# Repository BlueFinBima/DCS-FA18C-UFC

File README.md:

# DCS-FA18C-UFC
### This is a hardware and software project to build an Up Front Controller for the DCS F/A-18C Hornet

### Notes

The HT16K33 isn't too difficult to find, and can be picked up quite cheaply on AliExpress if you are prepared to wait.  The DLG2416 displays are quite expensive from 
typical vendors, however hunting around on ebay etc might result in more affordable sources.  They have a fixed character set which is unfortunate, however they remain useable and pleasing alternative to the 16 segment displays which the actual UFC requires.  If didn't manage to find suitable 16 segment displays of a physical size to work with this 
project.  The comms channel indicators are 16 segment displays (be careful not to buy 14 segment) but unfortunately I was unable to find displays which were not slanted - for me a minor issue.
* The ESP32 boards come in all sorts of shapes and sizes, and my controller board needs
a particular type of 38-pin board and I found to my cost that there were several boards with different widths.  I would expect [these boards](https://www.amazon.co.uk/AZDelivery-NodeMcu-CP2102-Development-including/dp/B074RGW2VQ/) to be the correct size.
* The green 16 segment LED displays now (2020) seem to be very hard to acquire.
* R2 and R5 on the controller board should only be installed as a last resort of the I2C is not stable without them
* The PCF8575 is a PCF8575PWR (TSSOP)
* D1 and D2 are BAT54CDW and not BAT54TW

### The Story
I would love to have a full Simpit for every aircraft – who
wouldn’t – but space / time / money all conspire against this.  I personally
feel that there is more immersion from the sensation of real switches, knobs
etc, but compromises are part of life.

I wanted a mix of virtual cockpit and some real devices so I
wrote a native F/A-18C interface for Helios, and I started a project to create
a hardware Up Front Controller.  This is what I am presenting here.   While the
3D printed UFC enclosure is very rough, hopefully you’ll get the idea of what I
am doing.  The UFC just has power going to it, and it has the potential to
drive future parts of the cockpit via i2c (I am aware of the limitations and
potential problems with the approach of using i2c, but it seems reliable in my
set up).   The UFC is controlled by an ESP32 board to get me the direct pins
and interrupts that I needed for the encoders.  Because there is only a single
power connecter to the UFC, it means that it can be removed from the set up
extremely quickly.  Likewise, the Thrustmaster Cougar MFDs are also very easy
to remove as they simply hang from the top of the screen, primarily to allow
hiding of the USB cables.  I rotated the rocker switches and 3D printed the
hangers so the MFDs sit over the top corners of the 23 inch Dell touch screen.

The UFC itself is pretty simple using DLG2416 displays (I
like the dots).  Unfortunately these do not have any programmable characters,
but the result is OK IMHO.  I would have preferred  16 and 7 segment displays,
but I could not find suitable devices.  The Comm Channel displays are 16
segment LED displays driven by the same HT16K33 that reads the keys and
switches.  Other things I would change if I ever revised the UFC design would
be to replace the 2 x volumes and the brightness knob with potentiometers and
put an i2c ADC onto the board – but I am happy enough with the encoders in the
current design that I’m not planning to do this.

I’m going to put a third Cougar MFD in for the AMPCD, but
I’m still considering how I can do this while keeping the mounting discrete.

#### 2020 Project Update
With two inidividuals (that I know of) successfully recreating this project, I chose to revisit
the facial.  I purchased a small SLA 3D printer which allowed me to print smaller key caps, and 
I was able to paint and use my 2.5W LED Laser to label these.  I also created new comm channel
selectors, as well as more harmonious knobs (ie not Mil Spec accurate) for the UFC.
My LED laser will not touch acrylic other than black, so the facia was cut from that material and 
white polystyrene sheet was then glued to the surface, and painted black.  The LED laser was then 
used to create the lettering.  While all of this is an improvement, I have to confess to not being 
very happy with this.   This is in part why the GitHub project has not been updated with these changes.

#### Thoughts about the future (July 2021)
Are there going to be further revisions to this project?  Well maybe.  I am considering a V3, primarily 
to see if I can improve the visuals of the displays, and to see if I can gain some level of crossover with
the AV-8B which has a similar UFC.  DLG2416's are expensive and difficult to get hold of.  16 segment LED displays
are also out of fashion, and green ones seem extremely rare.  I have created Eagle drawings for discrete 0603 / 0402
LED displays which can be charlieplexed and might be coaxed into looking like the 16-segment displays used in the 
real UFC.  I just need to finalise these plans, and pluck up the courage to use a PCBA service to build a prototype 
(I have neither the patience nor the skill to solder the volume to LEDs needed).  If I get around to getting a 
display prototyped *AND* I can work out how to make it look fit for purpose, then I will almost certainly begin
some work on a V3 of this UFC.

Controlling the very large number of LEDs will also be interesting, but I have been doing some prototyping and it does look possible.

### The History of this Project

I started out many years ago with the A-10C and Loz’s
profile for Helios which was a a great place to start.  After a while, I built
a real caution panel based on the Holtek HT16K33 which was driven by an Arduino
Pro Micro which communicated via a serial connection to a c# program which
talked to DCS.  Over time, the A-10C parts grew a bit and I had CMSC, CMSP,
UFC, NMSP and a few other panels.

The EOS project was a little too complex for my needs, and
while DCS-BIOS is a fantastic option, for a number of reasons, I have chosen to
stick with my own technology.

Fast forward a few years, and the Pro Micro and c# program
were replaced by an ESP8266 with more memory so that it had the capacity to do
all of the parsing needed and the wifi communication allowed direct connection
to the DCS exports.lua.  This was later replaced by an ESP32 board.

When the Hornet came out, I decided that I again wanted to
have a hybrid Helios cockpit, but I have always taken the view that offloading
as much work from my DCS PC so that it can concentrate  resources on DCS, was a
good thing.  Since I always have access to under-utilised PCs, I wanted the
virtual cockpit to be on a remote machine like I had with the A-10C. 
Unfortunately this ruled out Capt Zeen’s Hornet profile because it uses
keyboard commands which appear on the wrong PC, and the use of the A-10C Helios
interface requires a lot of processing in the exports.lua on the DCS machine.

I’m happy to make 3D parts visible on Fusion 360 on request.  Schematics etc are
Eagle format.

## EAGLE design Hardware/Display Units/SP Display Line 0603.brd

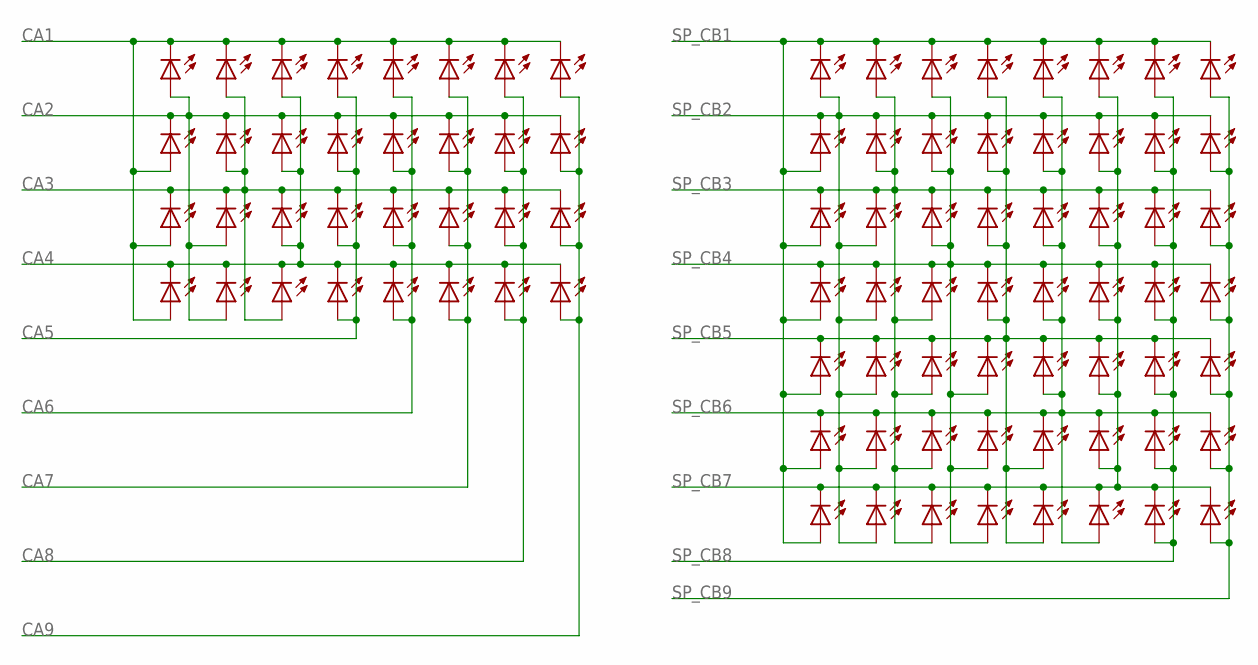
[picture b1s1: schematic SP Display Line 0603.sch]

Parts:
LED_A1, LED_A2: LEDSMT0603_1; CHIPLED_0603
LED_B1, LED_B2: LEDSMT0603_1; CHIPLED_0603
LED_C1, LED_C2: LEDSMT0603_1; CHIPLED_0603
LED_D1, LED_D2: LEDSMT0603_1; CHIPLED_0603
LED_DA1, LED_DA2, LED_DA3, LED_DA4, LED_DA5, LED_DA6, LED_DA7: LEDSMT0603_1; CHIPLED_0603
LED_DB1, LED_DB2, LED_DB3, LED_DB4, LED_DB5, LED_DB6, LED_DB7: LEDSMT0603_1; CHIPLED_0603
LED_DC1, LED_DC2, LED_DC3, LED_DC4, LED_DC5, LED_DC6, LED_DC7: LEDSMT0603_1; CHIPLED_0603
LED_DD1, LED_DD2, LED_DD3, LED_DD4, LED_DD5, LED_DD6, LED_DD7: LEDSMT0603_1; CHIPLED_0603
LED_DE1, LED_DE2, LED_DE3, LED_DE4, LED_DE5, LED_DE6, LED_DE7: LEDSMT0603_1; CHIPLED_0603
LED_DF1, LED_DF2, LED_DF3, LED_DF4, LED_DF5, LED_DF6, LED_DF7: LEDSMT0603_1; CHIPLED_0603
LED_DG1, LED_DG2, LED_DG3, LED_DG4, LED_DG5, LED_DG6, LED_DG7: LEDSMT0603_1; CHIPLED_0603
LED_DP1, LED_DP2, LED_DP3, LED_DP4, LED_DP5, LED_DP6, LED_DP7: LEDSMT0603_1; CHIPLED_0603
LED_E1, LED_E2: LEDSMT0603_1; CHIPLED_0603
LED_F1, LED_F2: LEDSMT0603_1; CHIPLED_0603
LED_G1, LED_G2: LEDSMT0603_1; CHIPLED_0603
LED_H1, LED_H2: LEDSMT0603_1; CHIPLED_0603
LED_K1, LED_K2: LEDSMT0603_1; CHIPLED_0603
LED_M1, LED_M2: LEDSMT0603_1; CHIPLED_0603
LED_N1, LED_N2: LEDSMT0603_1; CHIPLED_0603
LED_P1, LED_P2: LEDSMT0603_1; CHIPLED_0603
LED_R1, LED_R2: LEDSMT0603_1; CHIPLED_0603
LED_S1, LED_S2: LEDSMT0603_1; CHIPLED_0603
LED_T1, LED_T2: LEDSMT0603_1; CHIPLED_0603
LED_U1, LED_U2: LEDSMT0603_1; CHIPLED_0603

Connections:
CA1: LED_A1.C, LED_A2.A, LED_B1.C, LED_C1.C, LED_D1.C, LED_E1.C, LED_F1.C, LED_G1.C, LED_H1.C, LED_K1.A, LED_K2.A
CA2: LED_A1.A, LED_B2.A, LED_K1.C, LED_M1.C, LED_M2.A, LED_N1.C, LED_P1.C, LED_R1.C, LED_S1.C, LED_T1.C, LED_U1.C
CA3: LED_A2.C, LED_B1.A, LED_B2.C, LED_C2.C, LED_D2.C, LED_E2.C, LED_F2.C, LED_G2.C, LED_H2.C, LED_M1.A, LED_N2.A
CA4: LED_C1.A, LED_C2.A, LED_K2.C, LED_M2.C, LED_N1.A, LED_N2.C, LED_P2.C, LED_R2.C, LED_S2.C, LED_T2.C, LED_U2.C
CA5: LED_D1.A, LED_D2.A, LED_P1.A, LED_P2.A
CA6: LED_E1.A, LED_E2.A, LED_R1.A, LED_R2.A
CA7: LED_F1.A, LED_F2.A, LED_S1.A, LED_S2.A
CA8: LED_G1.A, LED_G2.A, LED_T1.A, LED_T2.A
CA9: LED_H1.A, LED_H2.A, LED_U1.A, LED_U2.A
SP_CB1: LED_DA1.C, LED_DA2.A, LED_DA3.A, LED_DA4.A, LED_DA5.A, LED_DA6.A, LED_DA7.A, LED_DB1.C, LED_DC1.C, LED_DD1.C, LED_DE1.C, LED_DF1.C, LED_DG1.C, LED_DP1.C
SP_CB2: LED_DA1.A, LED_DA2.C, LED_DB2.C, LED_DB3.A, LED_DB4.A, LED_DB5.A, LED_DB6.A, LED_DB7.A, LED_DC2.C, LED_DD2.C, LED_DE2.C, LED_DF2.C, LED_DG2.C, LED_DP2.C
SP_CB3: LED_DA3.C, LED_DB1.A, LED_DB2.A, LED_DB3.C, LED_DC3.C, LED_DC4.A, LED_DC5.A, LED_DC6.A, LED_DC7.A, LED_DD3.C, LED_DE3.C, LED_DF3.C, LED_DG3.C, LED_DP3.C
SP_CB4: LED_DA4.C, LED_DB4.C, LED_DC1.A, LED_DC2.A, LED_DC3.A, LED_DC4.C, LED_DD4.C, LED_DD5.A, LED_DD6.A, LED_DD7.A, LED_DE4.C, LED_DF4.C, LED_DG4.C, LED_DP4.C
SP_CB5: LED_DA5.C, LED_DB5.C, LED_DC5.C, LED_DD1.A, LED_DD2.A, LED_DD3.A, LED_DD4.A, LED_DD5.C, LED_DE5.C, LED_DE6.A, LED_DE7.A, LED_DF5.C, LED_DG5.C, LED_DP5.C
SP_CB6: LED_DA6.C, LED_DB6.C, LED_DC6.C, LED_DD6.C, LED_DE1.A, LED_DE2.A, LED_DE3.A, LED_DE4.A, LED_DE5.A, LED_DE6.C, LED_DF6.C, LED_DF7.A, LED_DG6.C, LED_DP6.C
SP_CB7: LED_DA7.C, LED_DB7.C, LED_DC7.C, LED_DD7.C, LED_DE7.C, LED_DF1.A, LED_DF2.A, LED_DF3.A, LED_DF4.A, LED_DF5.A, LED_DF6.A, LED_DF7.C, LED_DG7.C, LED_DP7.C
SP_CB8: LED_DG1.A, LED_DG2.A, LED_DG3.A, LED_DG4.A, LED_DG5.A, LED_DG6.A, LED_DG7.A
SP_CB9: LED_DP1.A, LED_DP2.A, LED_DP3.A, LED_DP4.A, LED_DP5.A, LED_DP6.A, LED_DP7.A

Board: 4 copper layers, 88 parts (0 on the bottom side), 18 nets, no tracks yet.

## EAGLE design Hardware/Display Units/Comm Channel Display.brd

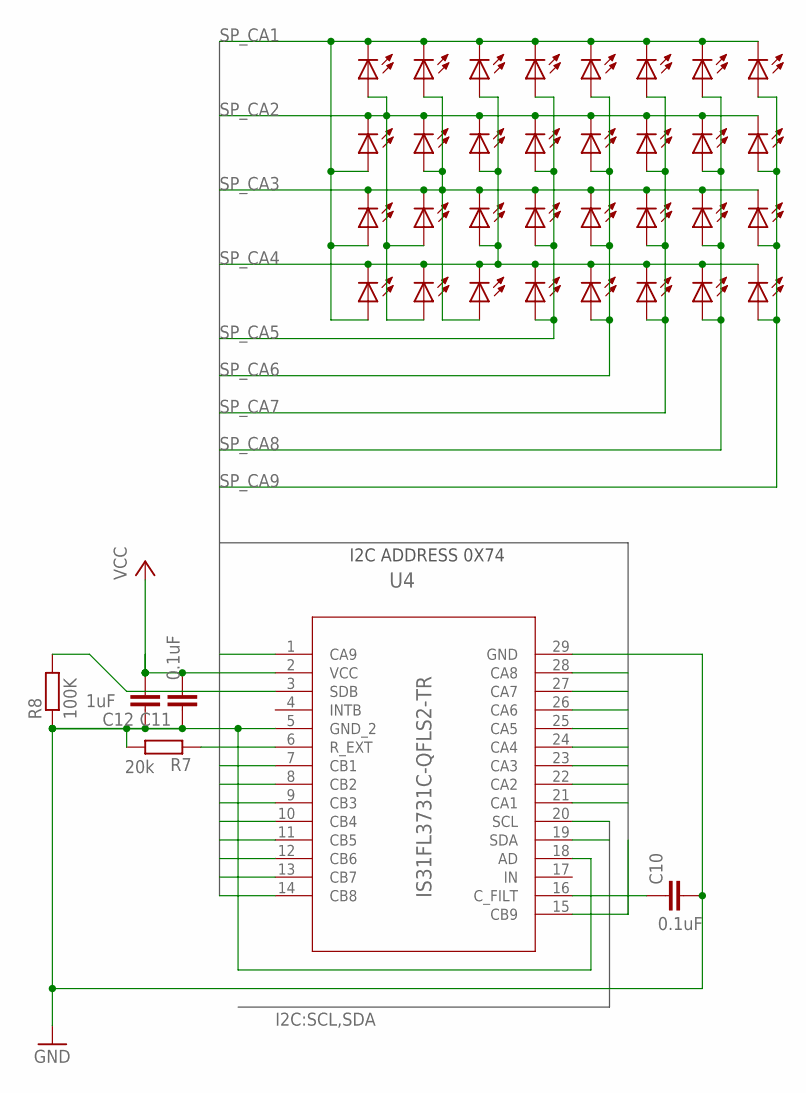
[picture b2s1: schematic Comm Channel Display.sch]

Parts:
C10: 0.1uF; C0201
C11: 0.1uF; C0402
C12: 1uF; C0402
LED_A3, LED_A4: LEDSMT0603_1; CHIPLED_0603
LED_B3, LED_B4: LEDSMT0603_1; CHIPLED_0603
LED_C3, LED_C4: LEDSMT0603_1; CHIPLED_0603
LED_D3, LED_D4: LEDSMT0603_1; CHIPLED_0603
LED_E3, LED_E4: LEDSMT0603_1; CHIPLED_0603
LED_F3, LED_F4: LEDSMT0603_1; CHIPLED_0603
LED_G3, LED_G4: LEDSMT0603_1; CHIPLED_0603
LED_H3, LED_H4: LEDSMT0603_1; CHIPLED_0603
LED_K3, LED_K4: LEDSMT0603_1; CHIPLED_0603
LED_M3, LED_M4: LEDSMT0603_1; CHIPLED_0603
LED_N3, LED_N4: LEDSMT0603_1; CHIPLED_0603
LED_P3, LED_P4: LEDSMT0603_1; CHIPLED_0603
LED_R3, LED_R4: LEDSMT0603_1; CHIPLED_0603
LED_S3, LED_S4: LEDSMT0603_1; CHIPLED_0603
LED_T3, LED_T4: LEDSMT0603_1; CHIPLED_0603
LED_U3, LED_U4: LEDSMT0603_1; CHIPLED_0603
R7: 20k; R0805
R8: 100K; R0201
U4: IS31FL3731C-QFLS2-TR; QFN-28_ISI

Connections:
GND: C10.2, C11.1, C12.1, R7.2, R8.1, U4.5 (GND_2), U4.18 (AD), U4.29 (GND)
unnamed: C10.1, U4.16 (C_FILT)
unnamed: R8.2, U4.3 (SDB)
unnamed: R7.1, U4.6 (R_EXT)
SCL: U4.20 (SCL)
SDA: U4.19 (SDA)
SP_CA1: LED_A3.C, LED_A4.A, LED_B3.C, LED_C3.C, LED_D3.C, LED_E3.C, LED_F3.C, LED_G3.C, LED_H3.C, LED_K3.A, LED_K4.A, U4.21 (CA1)
SP_CA2: LED_A3.A, LED_B4.A, LED_K3.C, LED_M3.C, LED_M4.A, LED_N3.C, LED_P3.C, LED_R3.C, LED_S3.C, LED_T3.C, LED_U3.C, U4.22 (CA2)
SP_CA3: LED_A4.C, LED_B3.A, LED_B4.C, LED_C4.C, LED_D4.C, LED_E4.C, LED_F4.C, LED_G4.C, LED_H4.C, LED_M3.A, LED_N4.A, U4.23 (CA3)
SP_CA4: LED_C3.A, LED_C4.A, LED_K4.C, LED_M4.C, LED_N3.A, LED_N4.C, LED_P4.C, LED_R4.C, LED_S4.C, LED_T4.C, LED_U4.C, U4.24 (CA4)
SP_CA5: LED_D3.A, LED_D4.A, LED_P3.A, LED_P4.A, U4.25 (CA5)
SP_CA6: LED_E3.A, LED_E4.A, LED_R3.A, LED_R4.A, U4.26 (CA6)
SP_CA7: LED_F3.A, LED_F4.A, LED_S3.A, LED_S4.A
SP_CA8: LED_G3.A, LED_G4.A, LED_T3.A, LED_T4.A, U4.28 (CA8)
SP_CA9: LED_H3.A, LED_H4.A, LED_U3.A, LED_U4.A, U4.1 (CA9)
SP_CB1: U4.7 (CB1)
SP_CB2: U4.8 (CB2)
SP_CB3: U4.9 (CB3)
SP_CB4: U4.10 (CB4)
SP_CB5: U4.11 (CB5)
SP_CB6: U4.12 (CB6)
SP_CB7: U4.13 (CB7), U4.27 (CA7)
SP_CB8: U4.14 (CB8)
SP_CB9: U4.15 (CB9)
VCC: C11.2, C12.2, U4.2 (VCC)

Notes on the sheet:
I2C ADDRESS 0X74

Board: 4 copper layers, 38 parts (0 on the bottom side), 15 nets, no tracks yet.

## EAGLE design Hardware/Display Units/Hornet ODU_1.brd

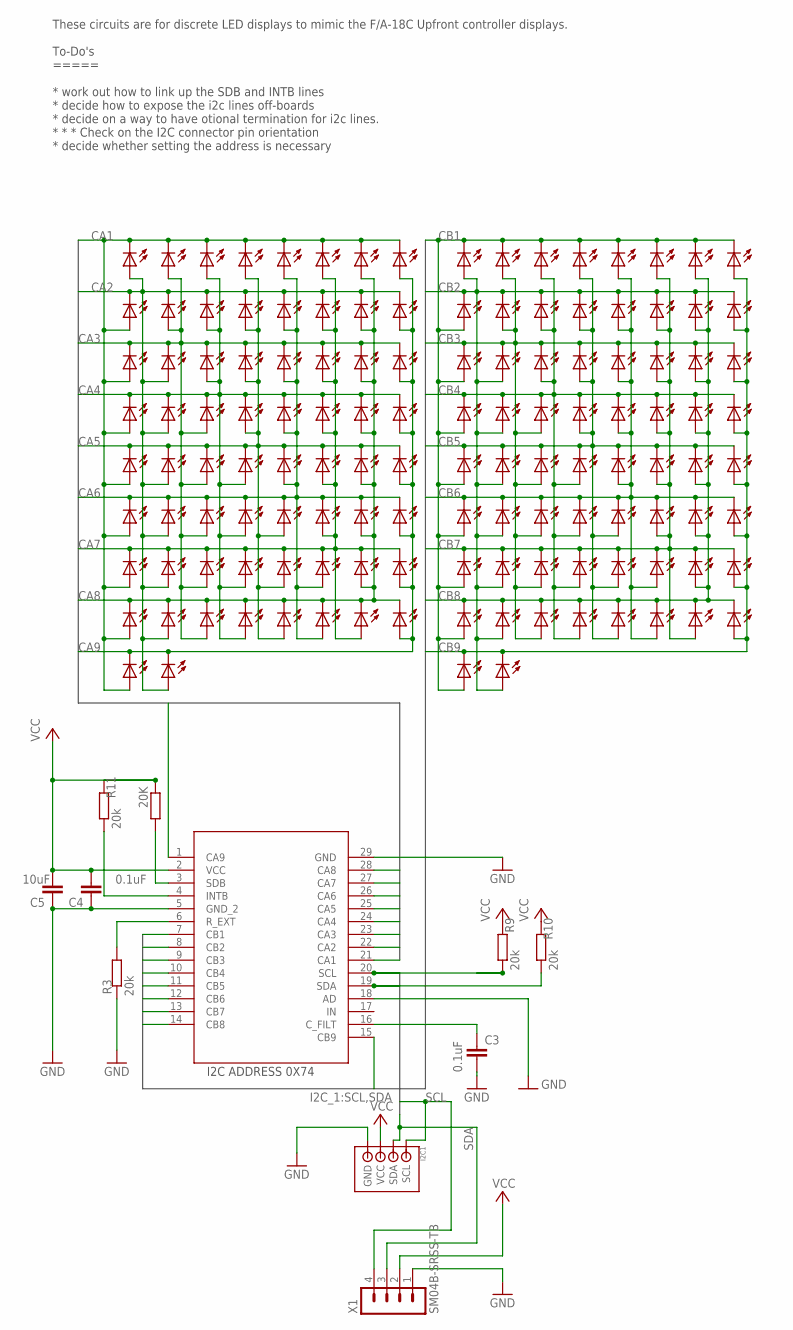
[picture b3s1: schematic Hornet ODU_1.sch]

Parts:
C3, C4: 0.1uF; C0805
C5: 10uF; C0805
I2C1: I2C_STEMMA_JST_PH_CONNECTORB4B-PH_STEMMA_I2C; B4B-PH-SOLDER
LED_A5, LED_A6, LED_A7, LED_A8, LED_A9, LED_A10, LED_A11, LED_A12: LEDSMT0603_1; CHIPLED_0603
LED_B5, LED_B6, LED_B7, LED_B8, LED_B9, LED_B10, LED_B11, LED_B12: LEDSMT0603_1; CHIPLED_0603
LED_C5, LED_C6, LED_C7, LED_C8, LED_C9, LED_C10, LED_C11, LED_C12: LEDSMT0603_1; CHIPLED_0603
LED_D5, LED_D6, LED_D7, LED_D8, LED_D9, LED_D10, LED_D11, LED_D12: LEDSMT0603_1; CHIPLED_0603
LED_E5, LED_E6, LED_E7, LED_E8, LED_E9, LED_E10, LED_E11, LED_E12: LEDSMT0603_1; CHIPLED_0603
LED_F5, LED_F6, LED_F7, LED_F8, LED_F9, LED_F10, LED_F11, LED_F12: LEDSMT0603_1; CHIPLED_0603
LED_G5, LED_G6, LED_G7, LED_G8, LED_G9, LED_G10, LED_G11, LED_G12: LEDSMT0603_1; CHIPLED_0603
LED_H5, LED_H6, LED_H7, LED_H8, LED_H9, LED_H10, LED_H11, LED_H12: LEDSMT0603_1; CHIPLED_0603
LED_K5, LED_K6, LED_K7, LED_K8, LED_K9, LED_K10, LED_K11, LED_K12: LEDSMT0603_1; CHIPLED_0603
LED_M5, LED_M6, LED_M7, LED_M8, LED_M9, LED_M10, LED_M11, LED_M12: LEDSMT0603_1; CHIPLED_0603
LED_N5, LED_N6, LED_N7, LED_N8, LED_N9, LED_N10, LED_N11, LED_N12: LEDSMT0603_1; CHIPLED_0603
LED_P5, LED_P6, LED_P7, LED_P8, LED_P9, LED_P10, LED_P11, LED_P12: LEDSMT0603_1; CHIPLED_0603
LED_R5, LED_R6, LED_R7, LED_R8, LED_R9, LED_R10, LED_R11, LED_R12: LEDSMT0603_1; CHIPLED_0603
LED_S5, LED_S6, LED_S7, LED_S8, LED_S9, LED_S10, LED_S11, LED_S12: LEDSMT0603_1; CHIPLED_0603
LED_SEL3, LED_SEL4, LED_SEL5, LED_SEL6: LEDSMT0603_1; CHIPLED_0603
LED_T5, LED_T6, LED_T7, LED_T8, LED_T9, LED_T10, LED_T11, LED_T12: LEDSMT0603_1; CHIPLED_0603
LED_U5, LED_U6, LED_U7, LED_U8, LED_U9, LED_U10, LED_U11, LED_U12: LEDSMT0603_1; CHIPLED_0603
R3, R9, R10, R11: 20k; R0805
R6: 20K; R0805
U1: IS31FL3731C-QFLS2-TR; QFN-28_ISI
X1: SM04B-SRSS-TB

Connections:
CA1: LED_A5.C, LED_A6.A, LED_A7.A, LED_A8.A, LED_B5.C, LED_C5.C, LED_D5.C, LED_E5.C, LED_F5.C, LED_G5.C, LED_H5.C, LED_K5.A, LED_K6.A, LED_K7.A, LED_K8.A, LED_SEL3.A, U1.21 (CA1)
CA2: LED_A5.A, LED_B6.A, LED_B7.A, LED_B8.A, LED_K5.C, LED_M5.C, LED_M6.A, LED_M7.A, LED_M8.A, LED_N5.C, LED_P5.C, LED_R5.C, LED_S5.C, LED_SEL4.A, LED_T5.C, LED_U5.C, U1.22 (CA2)
CA3: LED_A6.C, LED_B5.A, LED_B6.C, LED_C6.C, LED_C7.A, LED_C8.A, LED_D6.C, LED_E6.C, LED_F6.C, LED_G6.C, LED_H6.C, LED_M5.A, LED_N6.A, LED_N7.A, LED_N8.A, U1.23 (CA3)
CA4: LED_C5.A, LED_C6.A, LED_D7.A, LED_D8.A, LED_K6.C, LED_M6.C, LED_N5.A, LED_N6.C, LED_P6.C, LED_P7.A, LED_P8.A, LED_R6.C, LED_S6.C, LED_T6.C, LED_U6.C, U1.24 (CA4)
CA5: LED_A7.C, LED_B7.C, LED_C7.C, LED_D5.A, LED_D6.A, LED_D7.C, LED_E7.C, LED_E8.A, LED_F7.C, LED_G7.C, LED_H7.C, LED_P5.A, LED_P6.A, LED_R7.A, LED_R8.A, U1.25 (CA5)
CA6: LED_E5.A, LED_E6.A, LED_E7.A, LED_F8.A, LED_K7.C, LED_M7.C, LED_N7.C, LED_P7.C, LED_R5.A, LED_R6.A, LED_R7.C, LED_S7.C, LED_S8.A, LED_T7.C, LED_U7.C, U1.26 (CA6)
CA7: LED_A8.C, LED_B8.C, LED_C8.C, LED_D8.C, LED_E8.C, LED_F5.A, LED_F6.A, LED_F7.A, LED_F8.C, LED_G8.C, LED_H8.C, LED_S5.A, LED_S6.A, LED_S7.A, LED_T8.A, U1.27 (CA7)
CA8: LED_G5.A, LED_G6.A, LED_G7.A, LED_G8.A, LED_K8.C, LED_M8.C, LED_N8.C, LED_P8.C, LED_R8.C, LED_S8.C, LED_T5.A, LED_T6.A, LED_T7.A, LED_T8.C, LED_U8.C, U1.28 (CA8)
CA9: LED_H5.A, LED_H6.A, LED_H7.A, LED_H8.A, LED_SEL3.C, LED_SEL4.C, LED_U5.A, LED_U6.A, LED_U7.A, LED_U8.A, U1.1 (CA9)
CB1: LED_A9.C, LED_A10.A, LED_A11.A, LED_A12.A, LED_B9.C, LED_C9.C, LED_D9.C, LED_E9.C, LED_F9.C, LED_G9.C, LED_H9.C, LED_K9.A, LED_K10.A, LED_K11.A, LED_K12.A, LED_SEL5.A, U1.7 (CB1)
CB2: LED_A9.A, LED_B10.A, LED_B11.A, LED_B12.A, LED_K9.C, LED_M9.C, LED_M10.A, LED_M11.A, LED_M12.A, LED_N9.C, LED_P9.C, LED_R9.C, LED_S9.C, LED_SEL6.A, LED_T9.C, LED_U9.C, U1.8 (CB2)
CB3: LED_A10.C, LED_B9.A, LED_B10.C, LED_C10.C, LED_C11.A, LED_C12.A, LED_D10.C, LED_E10.C, LED_F10.C, LED_G10.C, LED_H10.C, LED_M9.A, LED_N10.A, LED_N11.A, LED_N12.A, U1.9 (CB3)
CB4: LED_C9.A, LED_C10.A, LED_D11.A, LED_D12.A, LED_K10.C, LED_M10.C, LED_N9.A, LED_N10.C, LED_P10.C, LED_P11.A, LED_P12.A, LED_R10.C, LED_S10.C, LED_T10.C, LED_U10.C, U1.10 (CB4)
CB5: LED_A11.C, LED_B11.C, LED_C11.C, LED_D9.A, LED_D10.A, LED_D11.C, LED_E11.C, LED_E12.A, LED_F11.C, LED_G11.C, LED_H11.C, LED_P9.A, LED_P10.A, LED_R11.A, LED_R12.A, U1.11 (CB5)
CB6: LED_E9.A, LED_E10.A, LED_E11.A, LED_F12.A, LED_K11.C, LED_M11.C, LED_N11.C, LED_P11.C, LED_R9.A, LED_R10.A, LED_R11.C, LED_S11.C, LED_S12.A, LED_T11.C, LED_U11.C, U1.12 (CB6)
CB7: LED_A12.C, LED_B12.C, LED_C12.C, LED_D12.C, LED_E12.C, LED_F9.A, LED_F10.A, LED_F11.A, LED_F12.C, LED_G12.C, LED_H12.C, LED_S9.A, LED_S10.A, LED_S11.A, LED_T12.A, U1.13 (CB7)
CB8: LED_G9.A, LED_G10.A, LED_G11.A, LED_G12.A, LED_K12.C, LED_M12.C, LED_N12.C, LED_P12.C, LED_R12.C, LED_S12.C, LED_T9.A, LED_T10.A, LED_T11.A, LED_T12.C, LED_U12.C, U1.14 (CB8)
CB9: LED_H9.A, LED_H10.A, LED_H11.A, LED_H12.A, LED_SEL5.C, LED_SEL6.C, LED_U9.A, LED_U10.A, LED_U11.A, LED_U12.A, U1.15 (CB9)
GND: C3.2, C4.1, C5.1, I2C1.P1 (GND), R3.2, U1.5 (GND_2), U1.18 (AD), U1.29 (GND), X1.1
unnamed: R3.1, U1.6 (R_EXT)
unnamed: C3.1, U1.16 (C_FILT)
unnamed: R6.2, U1.3 (SDB)
unnamed: R11.2, U1.4 (INTB)
SCL: I2C1.P4 (SCL), R9.2, U1.20 (SCL), X1.4
SDA: I2C1.P3 (SDA), R10.2, U1.19 (SDA), X1.3
VCC: C4.2, C5.2, I2C1.P2 (VCC), R6.1, R9.1, R10.1, R11.1, U1.2 (VCC), X1.2

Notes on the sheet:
I2C ADDRESS 0X74
These circuits are for discrete LED displays to mimic the F/A-18C Upfront controller displays. To-Do's ===== * work out how to link up the SDB and INTB lines * decide how to expose the i2c lines off-boards * decide on a way to have otional termination for i2c lines. * * * Check on the I2C connector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

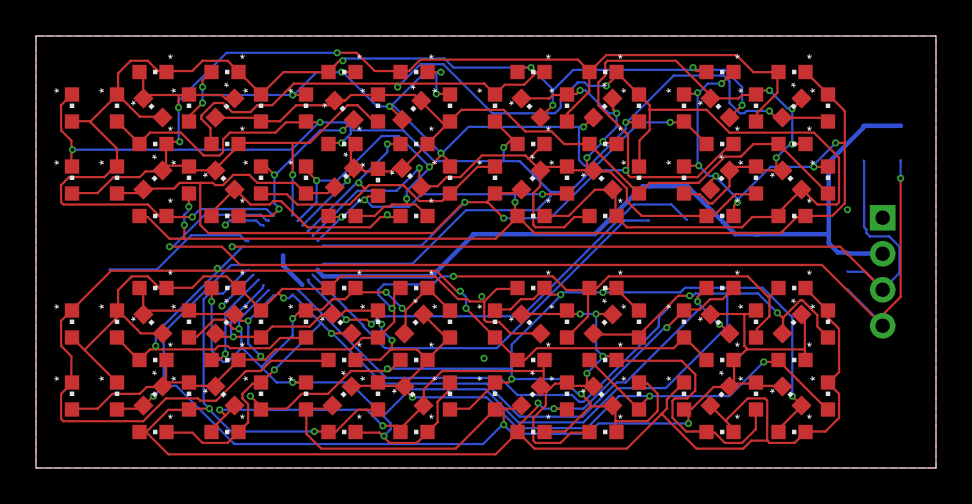
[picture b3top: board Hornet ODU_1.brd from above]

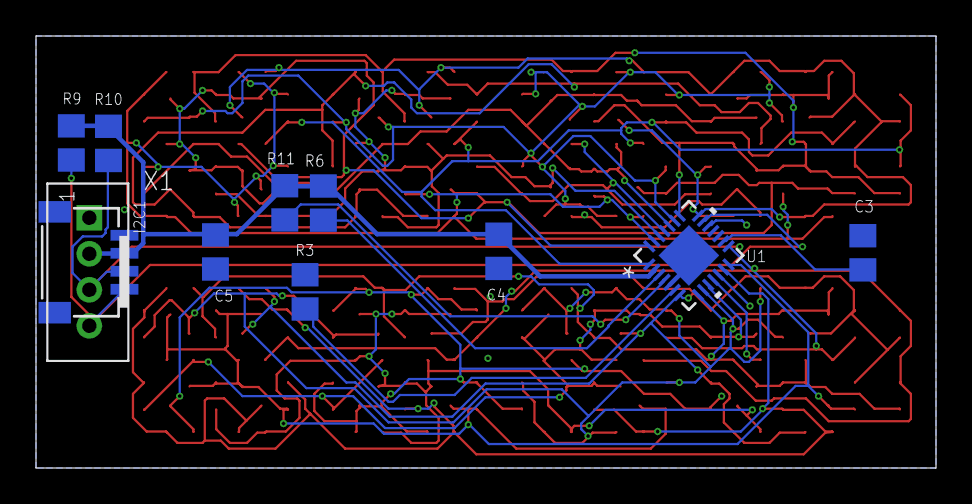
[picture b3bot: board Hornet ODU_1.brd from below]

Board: 4 copper layers, 50.0 x 24.0 mm, 143 parts (11 on the bottom side), 26 nets.

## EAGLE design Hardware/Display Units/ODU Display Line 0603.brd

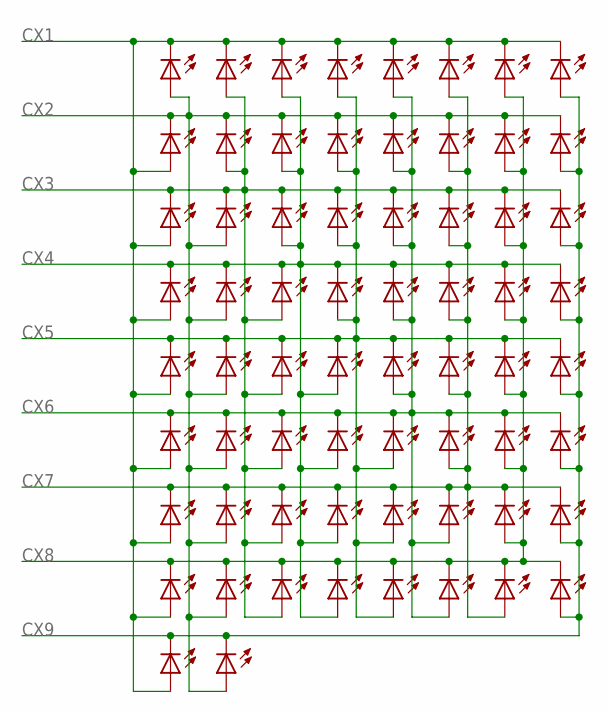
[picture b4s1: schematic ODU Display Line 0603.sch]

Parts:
LED_A1, LED_A2, LED_A3, LED_A4: LEDSMT0603_1; CHIPLED_0603
LED_B1, LED_B2, LED_B3, LED_B4: LEDSMT0603_1; CHIPLED_0603
LED_C1, LED_C2, LED_C3, LED_C4: LEDSMT0603_1; CHIPLED_0603
LED_D1, LED_D2, LED_D3, LED_D4: LEDSMT0603_1; CHIPLED_0603
LED_E1, LED_E2, LED_E3, LED_E4: LEDSMT0603_1; CHIPLED_0603
LED_F1, LED_F2, LED_F3, LED_F4: LEDSMT0603_1; CHIPLED_0603
LED_G1, LED_G2, LED_G3, LED_G4: LEDSMT0603_1; CHIPLED_0603
LED_H1, LED_H2, LED_H3, LED_H4: LEDSMT0603_1; CHIPLED_0603
LED_K1, LED_K2, LED_K3, LED_K4: LEDSMT0603_1; CHIPLED_0603
LED_M1, LED_M2, LED_M3, LED_M4: LEDSMT0603_1; CHIPLED_0603
LED_N1, LED_N2, LED_N3, LED_N4: LEDSMT0603_1; CHIPLED_0603
LED_P1, LED_P2, LED_P3, LED_P4: LEDSMT0603_1; CHIPLED_0603
LED_R1, LED_R2, LED_R3, LED_R4: LEDSMT0603_1; CHIPLED_0603
LED_S1, LED_S2, LED_S3, LED_S4: LEDSMT0603_1; CHIPLED_0603
LED_SEL1, LED_SEL2: LEDSMT0603_1; CHIPLED_0603
LED_T1, LED_T2, LED_T3, LED_T4: LEDSMT0603_1; CHIPLED_0603
LED_U1, LED_U2, LED_U3, LED_U4: LEDSMT0603_1; CHIPLED_0603

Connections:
CX1: LED_A1.C, LED_A2.A, LED_A3.A, LED_A4.A, LED_B1.C, LED_C1.C, LED_D1.C, LED_E1.C, LED_F1.C, LED_G1.C, LED_H1.C, LED_K1.A, LED_K2.A, LED_K3.A, LED_K4.A, LED_SEL1.A
CX2: LED_A1.A, LED_B2.A, LED_B3.A, LED_B4.A, LED_K1.C, LED_M1.C, LED_M2.A, LED_M3.A, LED_M4.A, LED_N1.C, LED_P1.C, LED_R1.C, LED_S1.C, LED_SEL2.A, LED_T1.C, LED_U1.C
CX3: LED_A2.C, LED_B1.A, LED_B2.C, LED_C2.C, LED_C3.A, LED_C4.A, LED_D2.C, LED_E2.C, LED_F2.C, LED_G2.C, LED_H2.C, LED_M1.A, LED_N2.A, LED_N3.A, LED_N4.A
CX4: LED_C1.A, LED_C2.A, LED_D3.A, LED_D4.A, LED_K2.C, LED_M2.C, LED_N1.A, LED_N2.C, LED_P2.C, LED_P3.A, LED_P4.A, LED_R2.C, LED_S2.C, LED_T2.C, LED_U2.C
CX5: LED_A3.C, LED_B3.C, LED_C3.C, LED_D1.A, LED_D2.A, LED_D3.C, LED_E3.C, LED_E4.A, LED_F3.C, LED_G3.C, LED_H3.C, LED_P1.A, LED_P2.A, LED_R3.A, LED_R4.A
CX6: LED_E1.A, LED_E2.A, LED_E3.A, LED_F4.A, LED_K3.C, LED_M3.C, LED_N3.C, LED_P3.C, LED_R1.A, LED_R2.A, LED_R3.C, LED_S3.C, LED_S4.A, LED_T3.C, LED_U3.C
CX7: LED_A4.C, LED_B4.C, LED_C4.C, LED_D4.C, LED_E4.C, LED_F1.A, LED_F2.A, LED_F3.A, LED_F4.C, LED_G4.C, LED_H4.C, LED_S1.A, LED_S2.A, LED_S3.A, LED_T4.A
CX8: LED_G1.A, LED_G2.A, LED_G3.A, LED_G4.A, LED_K4.C, LED_M4.C, LED_N4.C, LED_P4.C, LED_R4.C, LED_S4.C, LED_T1.A, LED_T2.A, LED_T3.A, LED_T4.C, LED_U4.C
CX9: LED_H1.A, LED_H2.A, LED_H3.A, LED_H4.A, LED_SEL1.C, LED_SEL2.C, LED_U1.A, LED_U2.A, LED_U3.A, LED_U4.A

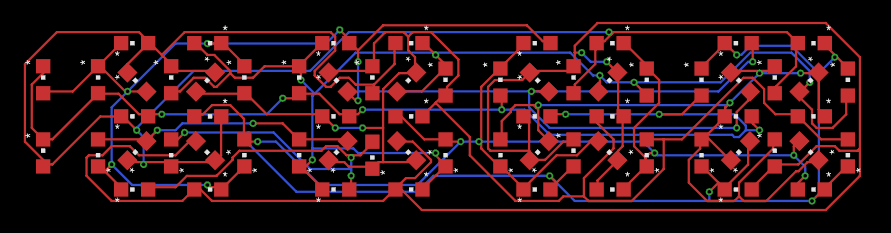
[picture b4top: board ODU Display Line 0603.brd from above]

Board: 4 copper layers, 66 parts (0 on the bottom side), 9 nets.

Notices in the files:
parts and their libraries:
microbuilder: This work is placed in the public domain, and may be freely used for commercial and non-commercial work with the following conditions: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
COPYRIGHT: Copyright (C) 2018 Accelerated Designs. All rights reserved
SparkFun-Aesthetics: Released under the Creative Commons
